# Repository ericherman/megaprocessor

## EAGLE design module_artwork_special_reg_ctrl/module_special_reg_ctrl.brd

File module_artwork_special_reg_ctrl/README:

Special Registers Control

This module generates the control signals for the Special Purpose
Registers module. To do this it uses information from the decoder
modules together with current state (and also the count in H for
iterative instructions) to work out what needs to be done this cycle.

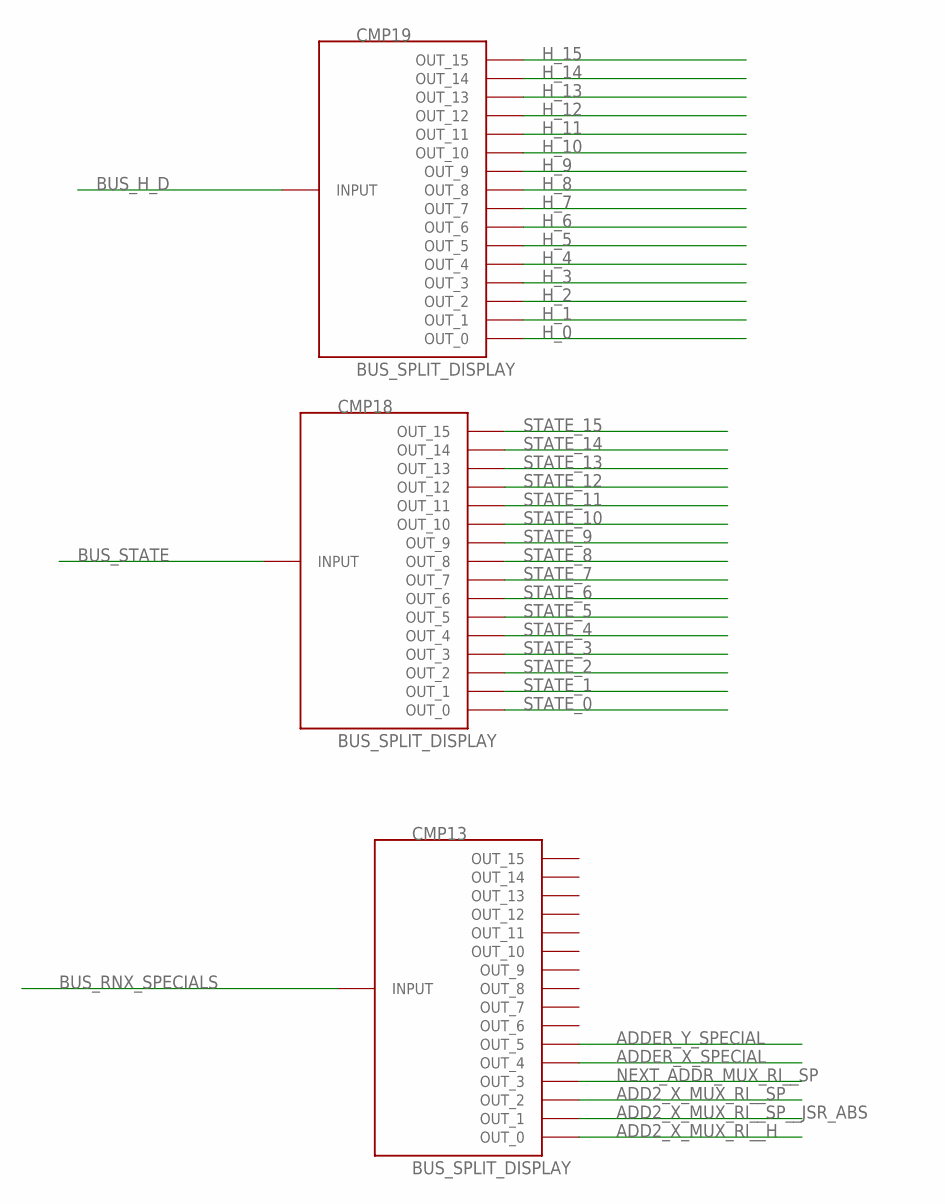
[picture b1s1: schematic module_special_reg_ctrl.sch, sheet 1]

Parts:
CMP13, CMP18, CMP19: BUS_SPLIT_DISPLAY

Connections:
ADD2_X_MUX_RI__H: CMP13.P$1 (OUT_0)
ADD2_X_MUX_RI__SP: CMP13.P$3 (OUT_2)
ADD2_X_MUX_RI__SP__JSR_ABS: CMP13.P$2 (OUT_1); also elsewhere on the board
ADDER_X_SPECIAL: CMP13.P$5 (OUT_4)
ADDER_Y_SPECIAL: CMP13.P$6 (OUT_5)
BUS_H_D: CMP19.INPUT
BUS_RNX_SPECIALS: CMP13.INPUT
BUS_STATE: CMP18.INPUT
H_0: CMP19.P$1 (OUT_0); also elsewhere on the board
H_1: CMP19.P$2 (OUT_1); also elsewhere on the board
H_2: CMP19.P$3 (OUT_2); also elsewhere on the board
H_3: CMP19.P$4 (OUT_3); also elsewhere on the board
H_4: CMP19.P$5 (OUT_4); also elsewhere on the board
H_5: CMP19.P$6 (OUT_5); also elsewhere on the board
H_6: CMP19.P$7 (OUT_6)
H_7: CMP19.P$8 (OUT_7)
H_8: CMP19.P$9 (OUT_8)
H_9: CMP19.P$10 (OUT_9)
H_10: CMP19.P$11 (OUT_10)
H_11: CMP19.P$12 (OUT_11)
H_12: CMP19.P$13 (OUT_12)
H_13: CMP19.P$14 (OUT_13)
H_14: CMP19.P$15 (OUT_14)
H_15: CMP19.P$16 (OUT_15)
NEXT_ADDR_MUX_RI__SP: CMP13.P$4 (OUT_3); also elsewhere on the board
STATE_0: CMP18.P$1 (OUT_0); also elsewhere on the board
STATE_1: CMP18.P$2 (OUT_1); also elsewhere on the board
STATE_2: CMP18.P$3 (OUT_2); also elsewhere on the board
STATE_3: CMP18.P$4 (OUT_3)
STATE_4: CMP18.P$5 (OUT_4); also elsewhere on the board
STATE_5: CMP18.P$6 (OUT_5); also elsewhere on the board
STATE_6: CMP18.P$7 (OUT_6); also elsewhere on the board
STATE_7: CMP18.P$8 (OUT_7); also elsewhere on the board
STATE_8: CMP18.P$9 (OUT_8); also elsewhere on the board
STATE_9: CMP18.P$10 (OUT_9); also elsewhere on the board
STATE_10: CMP18.P$11 (OUT_10); also elsewhere on the board
STATE_11: CMP18.P$12 (OUT_11); also elsewhere on the board
STATE_12: CMP18.P$13 (OUT_12); also elsewhere on the board
STATE_13: CMP18.P$14 (OUT_13); also elsewhere on the board
STATE_14: CMP18.P$15 (OUT_14)
STATE_15: CMP18.P$16 (OUT_15); also elsewhere on the board

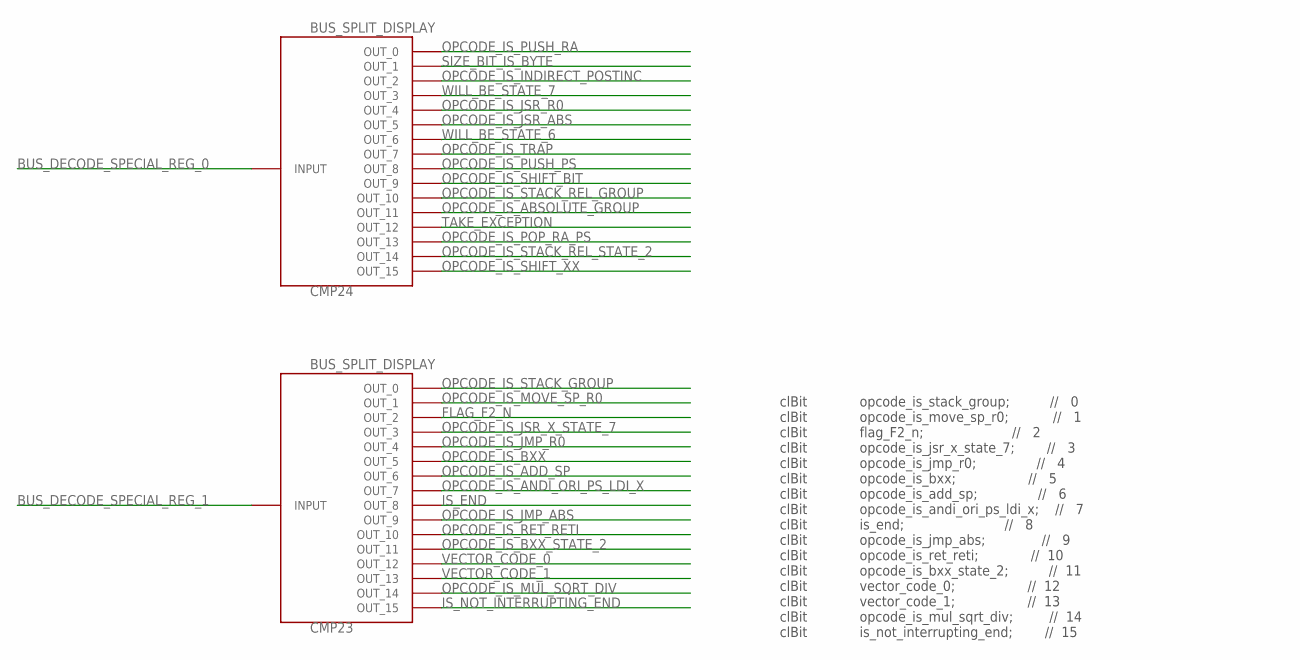
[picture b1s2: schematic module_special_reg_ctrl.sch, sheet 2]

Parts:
CMP23, CMP24: BUS_SPLIT_DISPLAY

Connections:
BUS_DECODE_SPECIAL_REG_0: CMP24.INPUT
BUS_DECODE_SPECIAL_REG_1: CMP23.INPUT
FLAG_F2_N: CMP23.P$3 (OUT_2); also elsewhere on the board
IS_END: CMP23.P$9 (OUT_8); also elsewhere on the board
IS_NOT_INTERRUPTING_END: CMP23.P$16 (OUT_15); also elsewhere on the board
OPCODE_IS_ABSOLUTE_GROUP: CMP24.P$12 (OUT_11); also elsewhere on the board
OPCODE_IS_ADD_SP: CMP23.P$7 (OUT_6); also elsewhere on the board
OPCODE_IS_ANDI_ORI_PS_LDI_X: CMP23.P$8 (OUT_7); also elsewhere on the board
OPCODE_IS_BXX: CMP23.P$6 (OUT_5); also elsewhere on the board
OPCODE_IS_BXX_STATE_2: CMP23.P$12 (OUT_11); also elsewhere on the board
OPCODE_IS_INDIRECT_POSTINC: CMP24.P$3 (OUT_2); also elsewhere on the board
OPCODE_IS_JMP_ABS: CMP23.P$10 (OUT_9); also elsewhere on the board
OPCODE_IS_JMP_R0: CMP23.P$5 (OUT_4); also elsewhere on the board
OPCODE_IS_JSR_ABS: CMP24.P$6 (OUT_5); also elsewhere on the board
OPCODE_IS_JSR_R0: CMP24.P$5 (OUT_4); also elsewhere on the board
OPCODE_IS_JSR_X_STATE_7: CMP23.P$4 (OUT_3); also elsewhere on the board
OPCODE_IS_MOVE_SP_R0: CMP23.P$2 (OUT_1); also elsewhere on the board
OPCODE_IS_MUL_SQRT_DIV: CMP23.P$15 (OUT_14); also elsewhere on the board
OPCODE_IS_POP_RA_PS: CMP24.P$14 (OUT_13); also elsewhere on the board
OPCODE_IS_PUSH_PS: CMP24.P$9 (OUT_8); also elsewhere on the board
OPCODE_IS_PUSH_RA: CMP24.P$1 (OUT_0); also elsewhere on the board
OPCODE_IS_RET_RETI: CMP23.P$11 (OUT_10); also elsewhere on the board
OPCODE_IS_SHIFT_BIT: CMP24.P$10 (OUT_9); also elsewhere on the board
OPCODE_IS_SHIFT_XX: CMP24.P$16 (OUT_15); also elsewhere on the board
OPCODE_IS_STACK_GROUP: CMP23.P$1 (OUT_0); also elsewhere on the board
OPCODE_IS_STACK_REL_GROUP: CMP24.P$11 (OUT_10); also elsewhere on the board
OPCODE_IS_STACK_REL_STATE_2: CMP24.P$15 (OUT_14); also elsewhere on the board
OPCODE_IS_TRAP: CMP24.P$8 (OUT_7); also elsewhere on the board
SIZE_BIT_IS_BYTE: CMP24.P$2 (OUT_1); also elsewhere on the board
TAKE_EXCEPTION: CMP24.P$13 (OUT_12); also elsewhere on the board
VECTOR_CODE_0: CMP23.P$13 (OUT_12); also elsewhere on the board
VECTOR_CODE_1: CMP23.P$14 (OUT_13); also elsewhere on the board
WILL_BE_STATE_6: CMP24.P$7 (OUT_6); also elsewhere on the board
WILL_BE_STATE_7: CMP24.P$4 (OUT_3); also elsewhere on the board

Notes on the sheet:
clBit opcode_is_stack_group; // 0 clBit opcode_is_move_sp_r0; // 1 clBit flag_F2_n; // 2 clBit opcode_is_jsr_x_state_7; // 3 clBit opcode_is_jmp_r0; // 4 clBit opcode_is_bxx; // 5 clBit opcode_is_add_sp; // 6 clBit opcode_is_andi_ori_ps_ldi_x; // 7 clBit is_end; // 8 clBit opcode_is_jmp_abs; // 9 c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

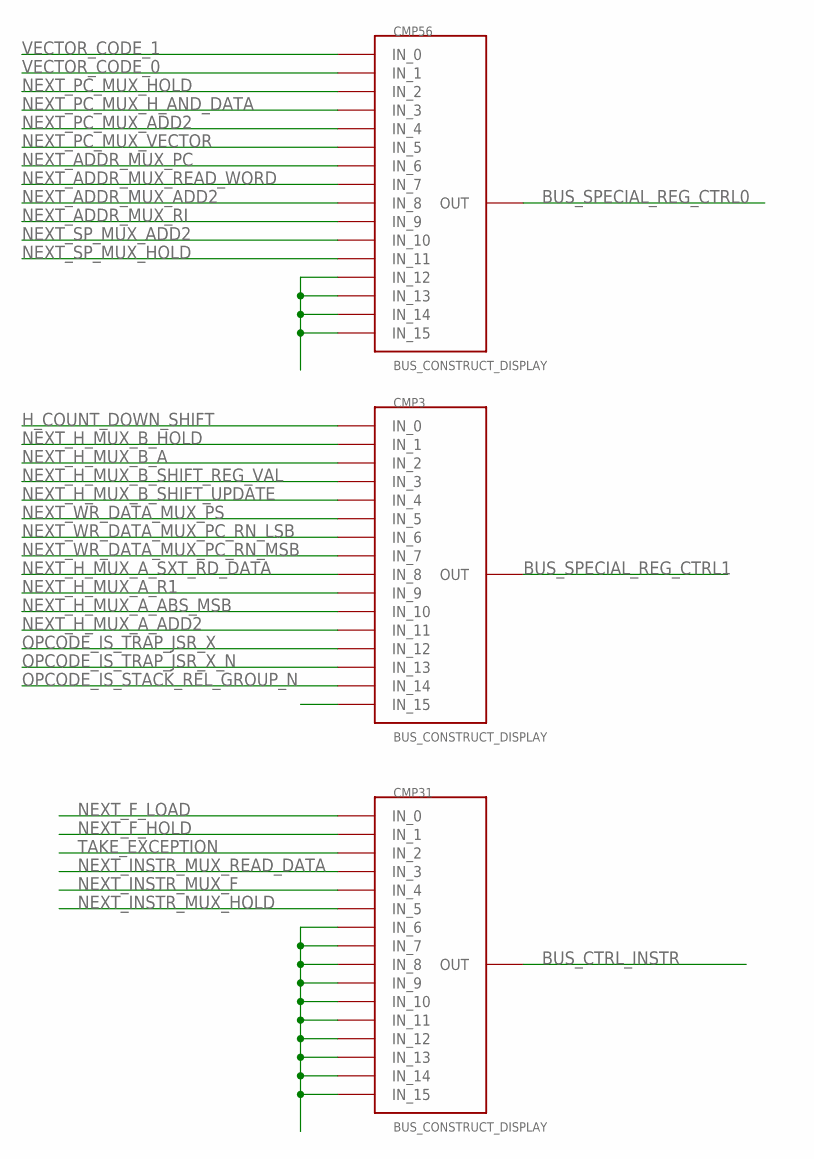
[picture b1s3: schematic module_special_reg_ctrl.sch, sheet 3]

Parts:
CMP3, CMP31, CMP56: BUS_CONSTRUCT_DISPLAY; BUS_SPLIT_DISPLAY

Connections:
BUS_CTRL_INSTR: CMP31.INPUT (OUT)
BUS_SPECIAL_REG_CTRL0: CMP56.INPUT (OUT)
BUS_SPECIAL_REG_CTRL1: CMP3.INPUT (OUT)
H_COUNT_DOWN_SHIFT: CMP3.P$1 (IN_0); also elsewhere on the board
unnamed: CMP56.P$13 (IN_12), CMP56.P$14 (IN_13), CMP56.P$15 (IN_14), CMP56.P$16 (IN_15)
unnamed: CMP31.P$7 (IN_6), CMP31.P$8 (IN_7), CMP31.P$9 (IN_8), CMP31.P$10 (IN_9), CMP31.P$11 (IN_10), CMP31.P$12 (IN_11), CMP31.P$13 (IN_12), CMP31.P$14 (IN_13), CMP31.P$15 (IN_14), CMP31.P$16 (IN_15)
NEXT_ADDR_MUX_ADD2: CMP56.P$9 (IN_8); also elsewhere on the board
NEXT_ADDR_MUX_PC: CMP56.P$7 (IN_6); also elsewhere on the board
NEXT_ADDR_MUX_READ_WORD: CMP56.P$8 (IN_7); also elsewhere on the board
NEXT_ADDR_MUX_RI: CMP56.P$10 (IN_9); also elsewhere on the board
NEXT_F_HOLD: CMP31.P$2 (IN_1); also elsewhere on the board
NEXT_F_LOAD: CMP31.P$1 (IN_0); also elsewhere on the board
NEXT_H_MUX_A_ABS_MSB: CMP3.P$11 (IN_10); also elsewhere on the board
NEXT_H_MUX_A_ADD2: CMP3.P$12 (IN_11); also elsewhere on the board
NEXT_H_MUX_A_R1: CMP3.P$10 (IN_9); also elsewhere on the board
NEXT_H_MUX_A_SXT_RD_DATA: CMP3.P$9 (IN_8); also elsewhere on the board
NEXT_H_MUX_B_A: CMP3.P$3 (IN_2); also elsewhere on the board
NEXT_H_MUX_B_HOLD: CMP3.P$2 (IN_1); also elsewhere on the board
NEXT_H_MUX_B_SHIFT_REG_VAL: CMP3.P$4 (IN_3); also elsewhere on the board
NEXT_H_MUX_B_SHIFT_UPDATE: CMP3.P$5 (IN_4); also elsewhere on the board
NEXT_INSTR_MUX_F: CMP31.P$5 (IN_4); also elsewhere on the board
NEXT_INSTR_MUX_HOLD: CMP31.P$6 (IN_5); also elsewhere on the board
NEXT_INSTR_MUX_READ_DATA: CMP31.P$4 (IN_3); also elsewhere on the board
NEXT_PC_MUX_ADD2: CMP56.P$5 (IN_4); also elsewhere on the board
NEXT_PC_MUX_HOLD: CMP56.P$3 (IN_2); also elsewhere on the board
NEXT_PC_MUX_H_AND_DATA: CMP56.P$4 (IN_3); also elsewhere on the board
NEXT_PC_MUX_VECTOR: CMP56.P$6 (IN_5); also elsewhere on the board
NEXT_SP_MUX_ADD2: CMP56.P$11 (IN_10); also elsewhere on the board
NEXT_SP_MUX_HOLD: CMP56.P$12 (IN_11); also elsewhere on the board
NEXT_WR_DATA_MUX_PC_RN_LSB: CMP3.P$7 (IN_6); also elsewhere on the board
NEXT_WR_DATA_MUX_PC_RN_MSB: CMP3.P$8 (IN_7); also elsewhere on the board
NEXT_WR_DATA_MUX_PS: CMP3.P$6 (IN_5); also elsewhere on the board
OPCODE_IS_STACK_REL_GROUP_N: CMP3.P$15 (IN_14); also elsewhere on the board
OPCODE_IS_TRAP_JSR_X: CMP3.P$13 (IN_12); also elsewhere on the board
OPCODE_IS_TRAP_JSR_X_N: CMP3.P$14 (IN_13); also elsewhere on the board
TAKE_EXCEPTION: CMP31.P$3 (IN_2); also elsewhere on the board
VECTOR_CODE_0: CMP56.P$2 (IN_1); also elsewhere on the board
VECTOR_CODE_1: CMP56.P$1 (IN_0); also elsewhere on the board

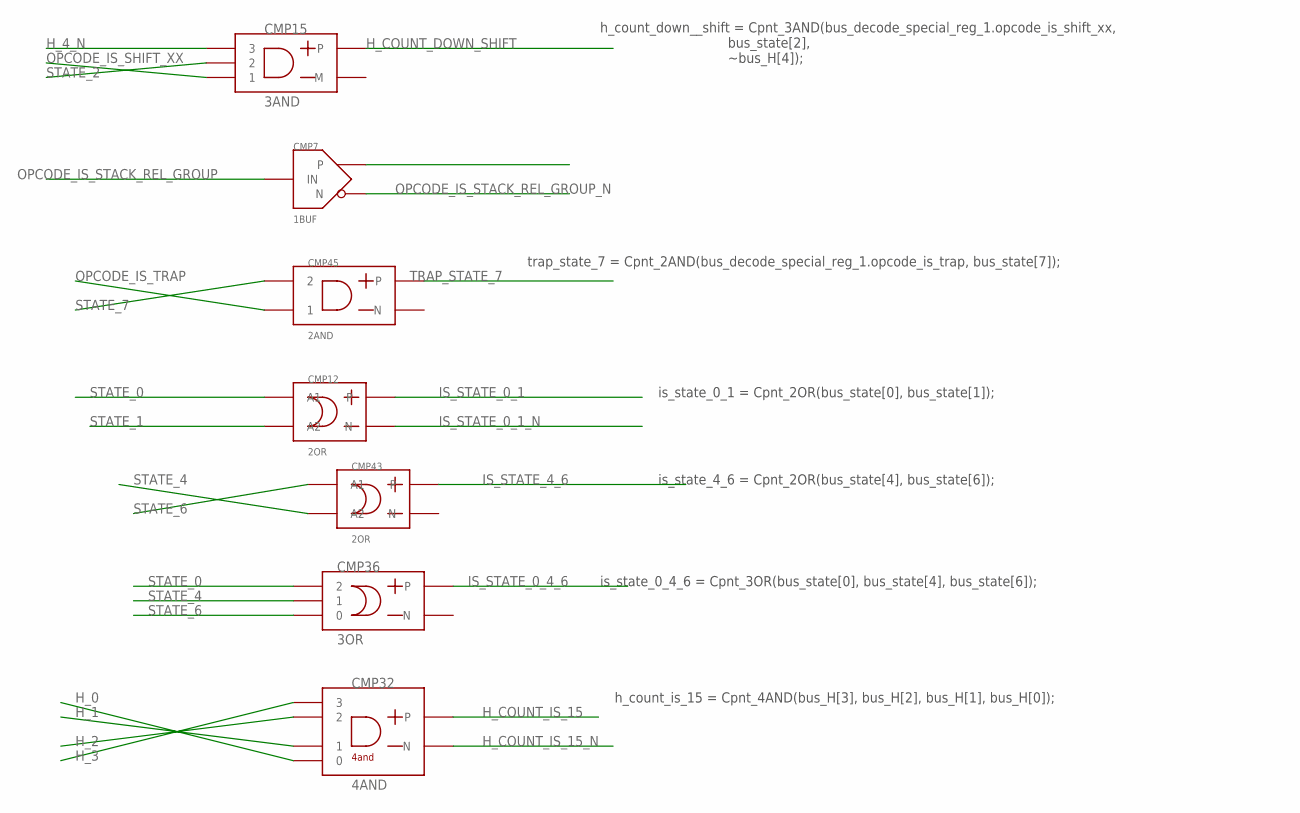
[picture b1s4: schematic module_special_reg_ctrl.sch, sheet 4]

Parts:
CMP7: 1BUF
CMP12, CMP43: 2OR
CMP15: 3AND
CMP32: 4AND
CMP36: 3OR
CMP45: 2AND

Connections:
H_0: CMP32.P$1 (0); also elsewhere on the board
H_1: CMP32.P$2 (1); also elsewhere on the board
H_2: CMP32.P$3 (2); also elsewhere on the board
H_3: CMP32.P$4 (3); also elsewhere on the board
H_4_N: CMP15.P$3 (3); also elsewhere on the board
H_COUNT_DOWN_SHIFT: CMP15.OUT_P; also elsewhere on the board
H_COUNT_IS_15: CMP32.OUT_P; also elsewhere on the board
H_COUNT_IS_15_N: CMP32.OUT_M (N); also elsewhere on the board
IS_STATE_0_1: CMP12.OUT_P; also elsewhere on the board
IS_STATE_0_1_N: CMP12.OUT_M (N); also elsewhere on the board
IS_STATE_0_4_6: CMP36.OUT_P; also elsewhere on the board
IS_STATE_4_6: CMP43.OUT_P; also elsewhere on the board
OPCODE_IS_SHIFT_XX: CMP15.P$1 (1); also elsewhere on the board
OPCODE_IS_STACK_REL_GROUP: CMP7.IN; also elsewhere on the board
OPCODE_IS_STACK_REL_GROUP_N: CMP7.N; also elsewhere on the board
OPCODE_IS_TRAP: CMP45.P$1 (1); also elsewhere on the board
STATE_0: CMP12.P$2 (A1), CMP36.P$3 (2); also elsewhere on the board
STATE_1: CMP12.P$1 (A2); also elsewhere on the board
STATE_2: CMP15.P$2 (2); also elsewhere on the board
STATE_4: CMP36.P$2 (1), CMP43.P$1 (A2); also elsewhere on the board
STATE_6: CMP36.P$1 (0), CMP43.P$2 (A1); also elsewhere on the board
STATE_7: CMP45.P$2 (2); also elsewhere on the board
TRAP_STATE_7: CMP45.OUT_P; also elsewhere on the board

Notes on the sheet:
h_count_down__shift = Cpnt_3AND(bus_decode_special_reg_1.opcode_is_shift_xx, bus_state[2], ~bus_H[4]);
trap_state_7 = Cpnt_2AND(bus_decode_special_reg_1.opcode_is_trap, bus_state[7]);
is_state_0_1 = Cpnt_2OR(bus_state[0], bus_state[1]);
is_state_4_6 = Cpnt_2OR(bus_state[4], bus_state[6]);
is_state_0_4_6 = Cpnt_3OR(bus_state[0], bus_state[4], bus_state[6]);
h_count_is_15 = Cpnt_4AND(bus_H[3], bus_H[2], bus_H[1], bus_H[0]);

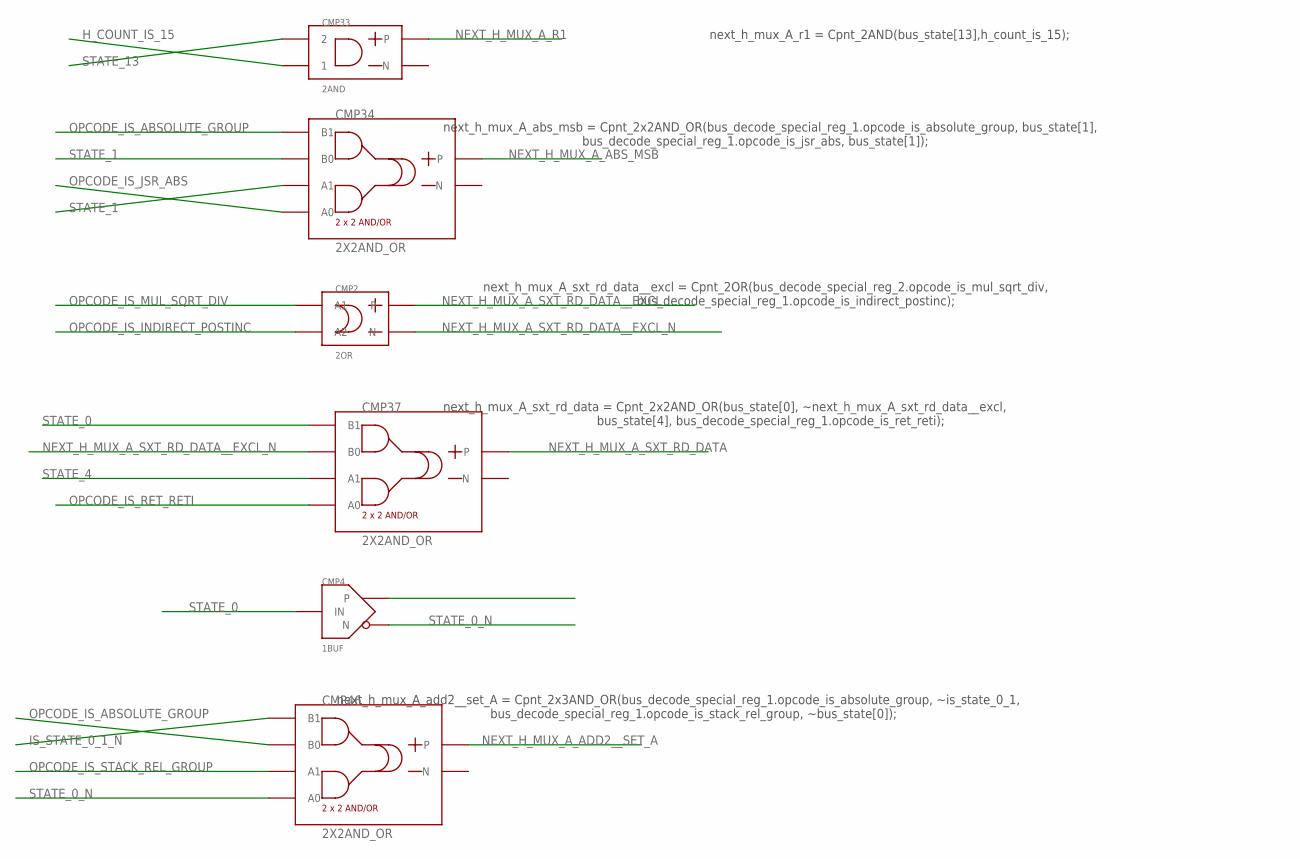
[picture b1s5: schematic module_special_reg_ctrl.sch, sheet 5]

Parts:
CMP2: 2OR
CMP4: 1BUF
CMP33: 2AND
CMP34, CMP37, CMP46: 2X2AND_OR

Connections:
H_COUNT_IS_15: CMP33.P$1 (1); also elsewhere on the board
IS_STATE_0_1_N: CMP46.P$4 (B1); also elsewhere on the board
NEXT_H_MUX_A_ABS_MSB: CMP34.OUT_P; also elsewhere on the board
NEXT_H_MUX_A_ADD2__SET_A: CMP46.OUT_P; also elsewhere on the board
NEXT_H_MUX_A_R1: CMP33.OUT_P; also elsewhere on the board
NEXT_H_MUX_A_SXT_RD_DATA: CMP37.OUT_P; also elsewhere on the board
NEXT_H_MUX_A_SXT_RD_DATA__EXCL: CMP2.OUT_P
NEXT_H_MUX_A_SXT_RD_DATA__EXCL_N: CMP2.OUT_M (N), CMP37.P$3 (B0)
OPCODE_IS_ABSOLUTE_GROUP: CMP34.P$4 (B1), CMP46.P$3 (B0); also elsewhere on the board
OPCODE_IS_INDIRECT_POSTINC: CMP2.P$1 (A2); also elsewhere on the board
OPCODE_IS_JSR_ABS: CMP34.P$1 (A0); also elsewhere on the board
OPCODE_IS_MUL_SQRT_DIV: CMP2.P$2 (A1); also elsewhere on the board
OPCODE_IS_RET_RETI: CMP37.P$1 (A0); also elsewhere on the board
OPCODE_IS_STACK_REL_GROUP: CMP46.P$2 (A1); also elsewhere on the board
STATE_0: CMP4.IN, CMP37.P$4 (B1); also elsewhere on the board
STATE_0_N: CMP4.N, CMP46.P$1 (A0)
STATE_1: CMP34.P$2 (A1), CMP34.P$3 (B0); also elsewhere on the board
STATE_4: CMP37.P$2 (A1); also elsewhere on the board
STATE_13: CMP33.P$2 (2); also elsewhere on the board

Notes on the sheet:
next_h_mux_A_r1 = Cpnt_2AND(bus_state[13],h_count_is_15);
next_h_mux_A_abs_msb = Cpnt_2x2AND_OR(bus_decode_special_reg_1.opcode_is_absolute_group, bus_state[1], bus_decode_special_reg_1.opcode_is_jsr_abs, bus_state[1]);
next_h_mux_A_sxt_rd_data__excl = Cpnt_2OR(bus_decode_special_reg_2.opcode_is_mul_sqrt_div, bus_decode_special_reg_1.opcode_is_indirect_postinc);
next_h_mux_A_sxt_rd_data = Cpnt_2x2AND_OR(bus_state[0], ~next_h_mux_A_sxt_rd_data__excl, bus_state[4], bus_decode_special_reg_1.opcode_is_ret_reti);
next_h_mux_A_add2__set_A = Cpnt_2x3AND_OR(bus_decode_special_reg_1.opcode_is_absolute_group, ~is_state_0_1, bus_decode_special_reg_1.opcode_is_stack_rel_group, ~bus_state[0]);

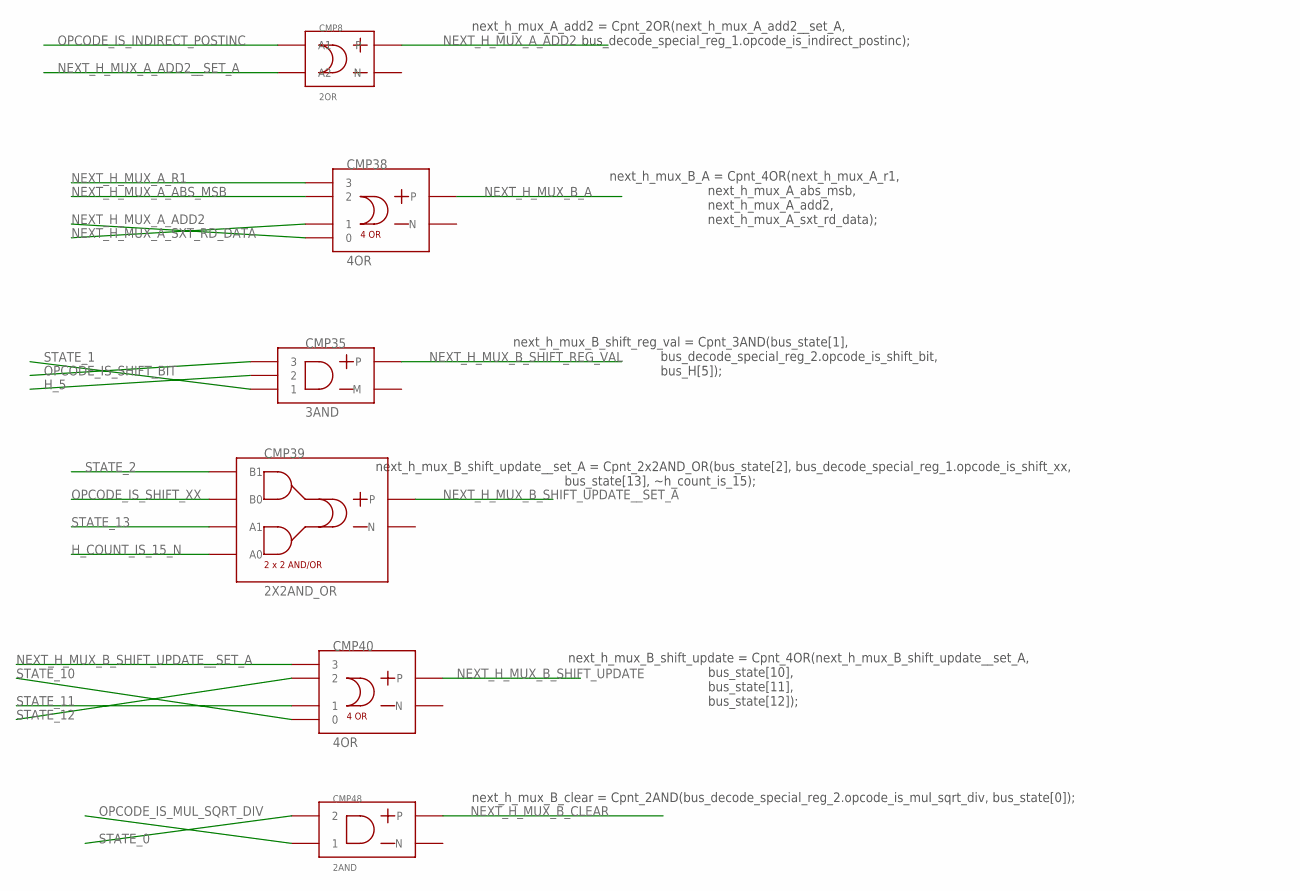
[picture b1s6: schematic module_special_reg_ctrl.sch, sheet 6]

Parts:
CMP8: 2OR
CMP35: 3AND
CMP38, CMP40: 4OR
CMP39: 2X2AND_OR
CMP48: 2AND

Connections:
H_5: CMP35.P$2 (2); also elsewhere on the board
H_COUNT_IS_15_N: CMP39.P$1 (A0); also elsewhere on the board
NEXT_H_MUX_A_ABS_MSB: CMP38.3 (2); also elsewhere on the board
NEXT_H_MUX_A_ADD2: CMP8.OUT_P, CMP38.1 (0); also elsewhere on the board
NEXT_H_MUX_A_ADD2__SET_A: CMP8.P$1 (A2); also elsewhere on the board
NEXT_H_MUX_A_R1: CMP38.4 (3); also elsewhere on the board
NEXT_H_MUX_A_SXT_RD_DATA: CMP38.2 (1); also elsewhere on the board
NEXT_H_MUX_B_A: CMP38.OUT_P; also elsewhere on the board
NEXT_H_MUX_B_CLEAR: CMP48.OUT_P; also elsewhere on the board
NEXT_H_MUX_B_SHIFT_REG_VAL: CMP35.OUT_P; also elsewhere on the board
NEXT_H_MUX_B_SHIFT_UPDATE: CMP40.OUT_P; also elsewhere on the board
NEXT_H_MUX_B_SHIFT_UPDATE__SET_A: CMP39.OUT_P, CMP40.4 (3)
OPCODE_IS_INDIRECT_POSTINC: CMP8.P$2 (A1); also elsewhere on the board
OPCODE_IS_MUL_SQRT_DIV: CMP48.P$1 (1); also elsewhere on the board
OPCODE_IS_SHIFT_BIT: CMP35.P$3 (3); also elsewhere on the board
OPCODE_IS_SHIFT_XX: CMP39.P$3 (B0); also elsewhere on the board
STATE_0: CMP48.P$2 (2); also elsewhere on the board
STATE_1: CMP35.P$1 (1); also elsewhere on the board
STATE_2: CMP39.P$4 (B1); also elsewhere on the board
STATE_10: CMP40.1 (0); also elsewhere on the board
STATE_11: CMP40.2 (1); also elsewhere on the board
STATE_12: CMP40.3 (2); also elsewhere on the board
STATE_13: CMP39.P$2 (A1); also elsewhere on the board

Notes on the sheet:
next_h_mux_A_add2 = Cpnt_2OR(next_h_mux_A_add2__set_A, bus_decode_special_reg_1.opcode_is_indirect_postinc);
next_h_mux_B_A = Cpnt_4OR(next_h_mux_A_r1, next_h_mux_A_abs_msb, next_h_mux_A_add2, next_h_mux_A_sxt_rd_data);
next_h_mux_B_shift_reg_val = Cpnt_3AND(bus_state[1], bus_decode_special_reg_2.opcode_is_shift_bit, bus_H[5]);
next_h_mux_B_shift_update__set_A = Cpnt_2x2AND_OR(bus_state[2], bus_decode_special_reg_1.opcode_is_shift_xx, bus_state[13], ~h_count_is_15);
next_h_mux_B_shift_update = Cpnt_4OR(next_h_mux_B_shift_update__set_A, bus_state[10], bus_state[11], bus_state[12]);
next_h_mux_B_clear = Cpnt_2AND(bus_decode_special_reg_2.opcode_is_mul_sqrt_div, bus_state[0]);

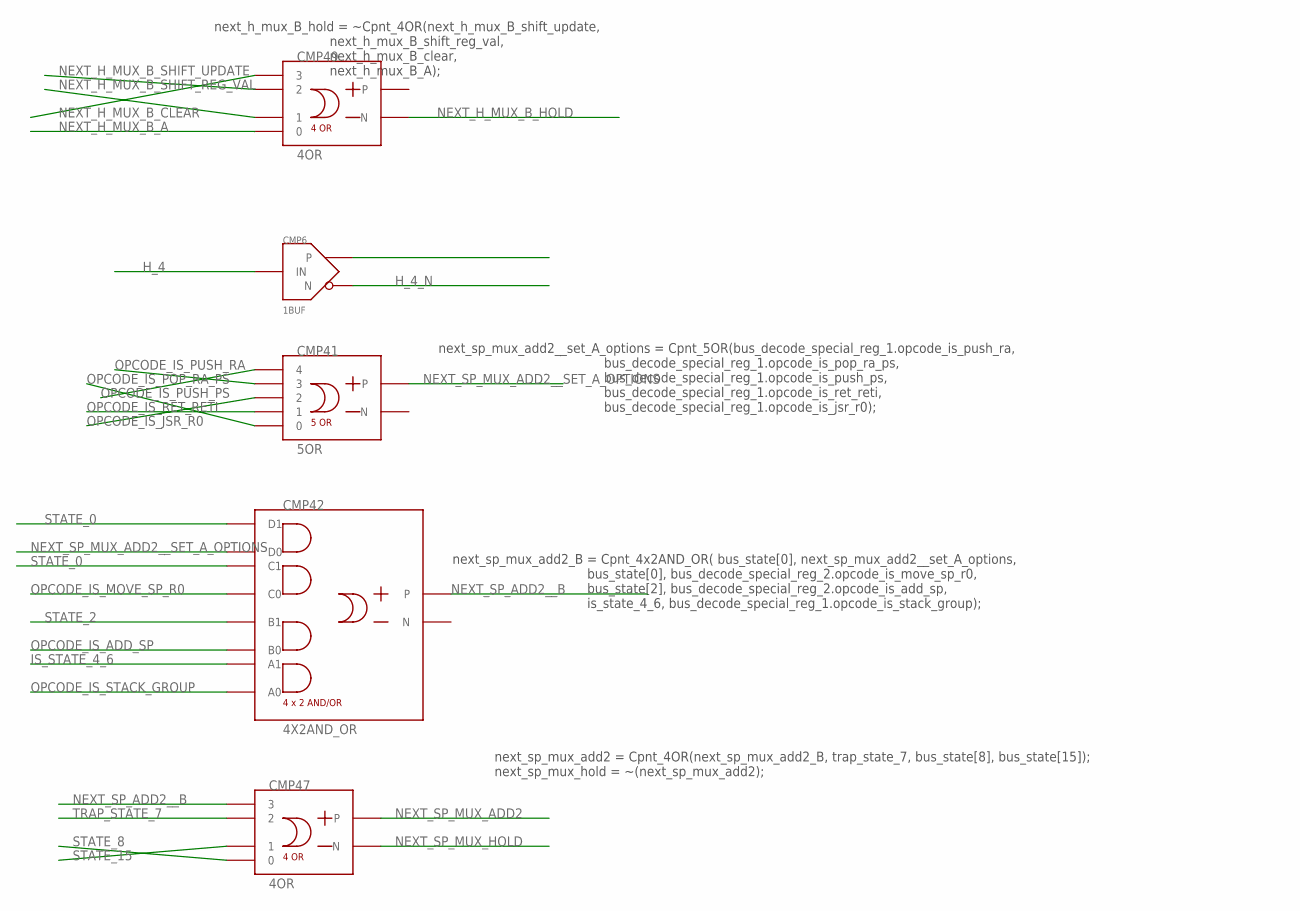
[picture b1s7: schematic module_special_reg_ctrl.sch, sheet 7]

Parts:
CMP6: 1BUF
CMP41: 5OR
CMP42: 4X2AND_OR
CMP47, CMP49: 4OR

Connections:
H_4: CMP6.IN; also elsewhere on the board
H_4_N: CMP6.N; also elsewhere on the board
IS_STATE_4_6: CMP42.P$2 (A1); also elsewhere on the board
NEXT_H_MUX_B_A: CMP49.1 (0); also elsewhere on the board
NEXT_H_MUX_B_CLEAR: CMP49.4 (3); also elsewhere on the board
NEXT_H_MUX_B_HOLD: CMP49.OUT_M (N); also elsewhere on the board
NEXT_H_MUX_B_SHIFT_REG_VAL: CMP49.2 (1); also elsewhere on the board
NEXT_H_MUX_B_SHIFT_UPDATE: CMP49.3 (2); also elsewhere on the board
NEXT_SP_ADD2__B: CMP42.OUT_P, CMP47.4 (3)
NEXT_SP_MUX_ADD2: CMP47.OUT_P; also elsewhere on the board
NEXT_SP_MUX_ADD2__SET_A_OPTIONS: CMP41.OUT_P, CMP42.P$7 (D0)
NEXT_SP_MUX_HOLD: CMP47.OUT_M (N); also elsewhere on the board
OPCODE_IS_ADD_SP: CMP42.P$3 (B0); also elsewhere on the board
OPCODE_IS_JSR_R0: CMP41.3 (2); also elsewhere on the board
OPCODE_IS_MOVE_SP_R0: CMP42.P$5 (C0); also elsewhere on the board
OPCODE_IS_POP_RA_PS: CMP41.1 (0); also elsewhere on the board
OPCODE_IS_PUSH_PS: CMP41.5 (4); also elsewhere on the board
OPCODE_IS_PUSH_RA: CMP41.4 (3); also elsewhere on the board
OPCODE_IS_RET_RETI: CMP41.2 (1); also elsewhere on the board
OPCODE_IS_STACK_GROUP: CMP42.P$1 (A0); also elsewhere on the board
STATE_0: CMP42.P$6 (C1), CMP42.P$8 (D1); also elsewhere on the board
STATE_2: CMP42.P$4 (B1); also elsewhere on the board
STATE_8: CMP47.1 (0); also elsewhere on the board
STATE_15: CMP47.2 (1); also elsewhere on the board
TRAP_STATE_7: CMP47.3 (2); also elsewhere on the board

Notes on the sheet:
next_h_mux_B_hold = ~Cpnt_4OR(next_h_mux_B_shift_update, next_h_mux_B_shift_reg_val, next_h_mux_B_clear, next_h_mux_B_A);
next_sp_mux_add2__set_A_options = Cpnt_5OR(bus_decode_special_reg_1.opcode_is_push_ra, bus_decode_special_reg_1.opcode_is_pop_ra_ps, bus_decode_special_reg_1.opcode_is_push_ps, bus_decode_special_reg_1.opcode_is_ret_reti, bus_decode_special_reg_1.opcode_is_jsr_r0);
next_sp_mux_add2_B = Cpnt_4x2AND_OR( bus_state[0], next_sp_mux_add2__set_A_options, bus_state[0], bus_decode_special_reg_2.opcode_is_move_sp_r0, bus_state[2], bus_decode_special_reg_2.opcode_is_add_sp, is_state_4_6, bus_decode_special_reg_1.opcode_is_stack_group);
next_sp_mux_add2 = Cpnt_4OR(next_sp_mux_add2_B, trap_state_7, bus_state[8], bus_state[15]); next_sp_mux_hold = ~(next_sp_mux_add2);

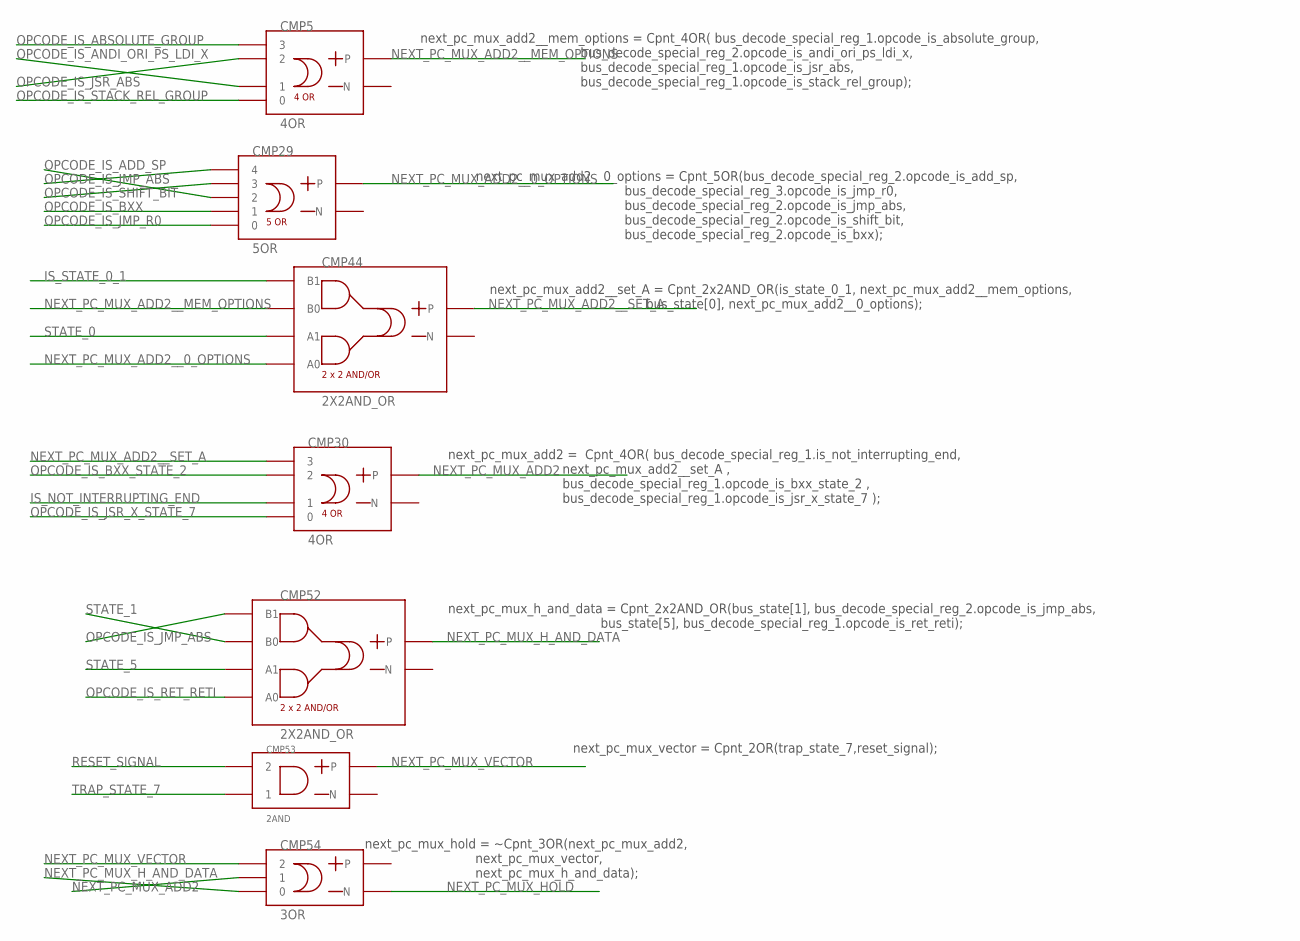
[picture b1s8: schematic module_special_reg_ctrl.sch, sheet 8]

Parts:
CMP5, CMP30: 4OR
CMP29: 5OR
CMP44, CMP52: 2X2AND_OR
CMP53: 2AND
CMP54: 3OR

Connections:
IS_NOT_INTERRUPTING_END: CMP30.2 (1); also elsewhere on the board
IS_STATE_0_1: CMP44.P$4 (B1); also elsewhere on the board
NEXT_PC_MUX_ADD2: CMP30.OUT_P, CMP54.P$2 (1); also elsewhere on the board
NEXT_PC_MUX_ADD2__0_OPTIONS: CMP29.OUT_P, CMP44.P$1 (A0)
NEXT_PC_MUX_ADD2__MEM_OPTIONS: CMP5.OUT_P, CMP44.P$3 (B0)
NEXT_PC_MUX_ADD2__SET_A: CMP30.4 (3), CMP44.OUT_P
NEXT_PC_MUX_HOLD: CMP54.OUT_M (N); also elsewhere on the board
NEXT_PC_MUX_H_AND_DATA: CMP52.OUT_P, CMP54.P$1 (0); also elsewhere on the board
NEXT_PC_MUX_VECTOR: CMP53.OUT_P, CMP54.P$3 (2); also elsewhere on the board
OPCODE_IS_ABSOLUTE_GROUP: CMP5.4 (3); also elsewhere on the board
OPCODE_IS_ADD_SP: CMP29.3 (2); also elsewhere on the board
OPCODE_IS_ANDI_ORI_PS_LDI_X: CMP5.2 (1); also elsewhere on the board
OPCODE_IS_BXX: CMP29.2 (1); also elsewhere on the board
OPCODE_IS_BXX_STATE_2: CMP30.3 (2); also elsewhere on the board
OPCODE_IS_JMP_ABS: CMP29.5 (4), CMP52.P$4 (B1); also elsewhere on the board
OPCODE_IS_JMP_R0: CMP29.1 (0); also elsewhere on the board
OPCODE_IS_JSR_ABS: CMP5.3 (2); also elsewhere on the board
OPCODE_IS_JSR_X_STATE_7: CMP30.1 (0); also elsewhere on the board
OPCODE_IS_RET_RETI: CMP52.P$1 (A0); also elsewhere on the board
OPCODE_IS_SHIFT_BIT: CMP29.4 (3); also elsewhere on the board
OPCODE_IS_STACK_REL_GROUP: CMP5.1 (0); also elsewhere on the board
RESET_SIGNAL: CMP53.P$2 (2)
STATE_0: CMP44.P$2 (A1); also elsewhere on the board
STATE_1: CMP52.P$3 (B0); also elsewhere on the board
STATE_5: CMP52.P$2 (A1); also elsewhere on the board
TRAP_STATE_7: CMP53.P$1 (1); also elsewhere on the board

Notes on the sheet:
next_pc_mux_add2__mem_options = Cpnt_4OR( bus_decode_special_reg_1.opcode_is_absolute_group, bus_decode_special_reg_2.opcode_is_andi_ori_ps_ldi_x, bus_decode_special_reg_1.opcode_is_jsr_abs, bus_decode_special_reg_1.opcode_is_stack_rel_group);
next_pc_mux_add2__0_options = Cpnt_5OR(bus_decode_special_reg_2.opcode_is_add_sp, bus_decode_special_reg_3.opcode_is_jmp_r0, bus_decode_special_reg_2.opcode_is_jmp_abs, bus_decode_special_reg_2.opcode_is_shift_bit, bus_decode_special_reg_2.opcode_is_bxx);
next_pc_mux_add2__set_A = Cpnt_2x2AND_OR(is_state_0_1, next_pc_mux_add2__mem_options, bus_state[0], next_pc_mux_add2__0_options);
next_pc_mux_add2 = Cpnt_4OR( bus_decode_special_reg_1.is_not_interrupting_end, next_pc_mux_add2__set_A , bus_decode_special_reg_1.opcode_is_bxx_state_2 , bus_decode_special_reg_1.opcode_is_jsr_x_state_7 );
next_pc_mux_h_and_data = Cpnt_2x2AND_OR(bus_state[1], bus_decode_special_reg_2.opcode_is_jmp_abs, bus_state[5], bus_decode_special_reg_1.opcode_is_ret_reti);
next_pc_mux_vector = Cpnt_2OR(trap_state_7,reset_signal);
next_pc_mux_hold = ~Cpnt_3OR(next_pc_mux_add2, next_pc_mux_vector, next_pc_mux_h_and_data);

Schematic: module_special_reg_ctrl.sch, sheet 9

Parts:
CMP9: 4OR
CMP10: 4X2AND_OR
CMP11: 5OR
CMP16, CMP67: 2AND
CMP22: 1BUF

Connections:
ADD2_X_MUX_RI__SP__JSR_ABS: CMP11.2 (1); also elsewhere on the board
FLAG_F2_N: CMP67.P$1 (1); also elsewhere on the board
IS_END: CMP22.IN; also elsewhere on the board
IS_END_N: CMP10.P$7 (D0), CMP22.N
IS_STATE_4_6: CMP10.P$5 (C0); also elsewhere on the board
NEXT_ADDR_MUX_ADD2: CMP11.OUT_P; also elsewhere on the board
NEXT_ADDR_MUX_ADD2__SET_A: CMP10.OUT_P, CMP11.5 (4)
NEXT_ADDR_MUX_ADD2__SET_A_OPTIONS: CMP9.OUT_P, CMP10.P$2 (A1), CMP10.P$3 (B0)
NEXT_ADDR_MUX_READ_WORD: CMP16.OUT_P; also elsewhere on the board
NON_RESET_TRAP: CMP9.4 (3), CMP67.OUT_P
OPCODE_IS_ABSOLUTE_GROUP: CMP10.P$6 (C1), CMP16.P$1 (1); also elsewhere on the board
OPCODE_IS_BXX_STATE_2: CMP11.4 (3); also elsewhere on the board
OPCODE_IS_JSR_R0: CMP9.1 (0); also elsewhere on the board
OPCODE_IS_PUSH_PS: CMP9.3 (2); also elsewhere on the board
OPCODE_IS_PUSH_RA: CMP9.2 (1); also elsewhere on the board
OPCODE_IS_STACK_REL_GROUP: CMP10.P$8 (D1); also elsewhere on the board
OPCODE_IS_TRAP: CMP67.P$2 (2); also elsewhere on the board
STATE_0: CMP10.P$4 (B1); also elsewhere on the board
STATE_1: CMP16.P$2 (2); also elsewhere on the board
STATE_6: CMP10.P$1 (A0); also elsewhere on the board
STATE_15: CMP11.1 (0); also elsewhere on the board
TRAP_STATE_7: CMP11.3 (2); also elsewhere on the board

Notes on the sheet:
non_reset_trap = Cpnt_2AND(bus_decode_special_reg_2.flag_F2_n, bus_decode_special_reg_1.opcode_is_trap);
next_addr_mux_add2__set_A_options = Cpnt_4OR(bus_decode_special_reg_1.opcode_is_jsr_r0, bus_decode_special_reg_1.opcode_is_push_ra, bus_decode_special_reg_1.opcode_is_push_ps, non_reset_trap);
next_addr_mux_add2__set_A = Cpnt_4x2AND_OR(next_addr_mux_add2__set_A_options,bus_state[0], next_addr_mux_add2__set_A_options,bus_state[6], bus_decode_special_reg_1.opcode_is_stack_rel_group, ~bus_decode_special_reg_2.is_end, bus_decode_special_reg_1.opcode_is_absolute_group, is_state_4_6);
next_addr_mux_add2 = Cpnt_5OR(next_addr_mux_add2__set_A, bus_decode_special_reg_2.opcode_is_bxx_state_2, bus_rnx_specials.add2_x_mux_ri__sp__jsr_abs, bus_state[15], trap_state_7);
next_addr_mux_read_word = Cpnt_2AND(bus_state[1], bus_decode_special_reg_1.opcode_is_absolute_group);

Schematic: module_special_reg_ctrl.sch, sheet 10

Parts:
CMP1, CMP61: 3OR
CMP20: 2X2AND_OR
CMP57: 2OR
CMP58: 5OR
CMP59, CMP60: 3AND
CMP62: 1BUF

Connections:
IS_END: CMP59.P$1 (1), CMP60.P$3 (3); also elsewhere on the board
IS_STATE_0_4_6: CMP20.P$4 (B1); also elsewhere on the board
NEXT_ADDR_MUX_ADD2: CMP1.P$2 (1); also elsewhere on the board
NEXT_ADDR_MUX_PC: CMP1.OUT_M (N); also elsewhere on the board
NEXT_ADDR_MUX_READ_WORD: CMP1.P$1 (0); also elsewhere on the board
NEXT_ADDR_MUX_RI: CMP1.P$3 (2), CMP20.OUT_P; also elsewhere on the board
NEXT_ADDR_MUX_RI__SP: CMP20.P$1 (A0), CMP20.P$2 (A1); also elsewhere on the board
NEXT_F_HOLD: CMP57.OUT_M (N); also elsewhere on the board
NEXT_F_LOAD: CMP57.OUT_P; also elsewhere on the board
NEXT_INSTR_MUX_F: CMP59.OUT_P, CMP61.P$3 (2); also elsewhere on the board
NEXT_INSTR_MUX_F_N: CMP59.OUT_M (M), CMP60.P$2 (2)
NEXT_INSTR_MUX_F__OPTIONS: CMP58.OUT_P, CMP59.P$2 (2)
NEXT_INSTR_MUX_HOLD: CMP61.OUT_M (N); also elsewhere on the board
NEXT_INSTR_MUX_READ_DATA: CMP60.OUT_P, CMP61.P$2 (1); also elsewhere on the board
OPCODE_IS_INDIRECT_POSTINC: CMP20.P$3 (B0), CMP58.2 (1); also elsewhere on the board
OPCODE_IS_POP_RA_PS: CMP58.5 (4); also elsewhere on the board
OPCODE_IS_PUSH_PS: CMP58.4 (3); also elsewhere on the board
OPCODE_IS_PUSH_RA: CMP58.1 (0); also elsewhere on the board
OPCODE_IS_STACK_REL_GROUP: CMP58.3 (2); also elsewhere on the board
OPCODE_IS_STACK_REL_STATE_2: CMP57.P$2 (A1); also elsewhere on the board
STATE_0: CMP57.P$1 (A2); also elsewhere on the board
TAKE_EXCEPTION: CMP61.P$1 (0), CMP62.IN; also elsewhere on the board
TAKE_EXCEPTION_N: CMP59.P$3 (3), CMP60.P$1 (1), CMP62.N

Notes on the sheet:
next_addr_mux_ri = Cpnt_2x2AND_OR(is_state_0_4_6, bus_decode_special_reg_1.opcode_is_indirect_postinc, bus_rnx_specials.next_addr_mux_ri__sp, bus_rnx_specials.next_addr_mux_ri__sp);
next_addr_mux_pc = ~Cpnt_3OR( next_addr_mux_ri , next_addr_mux_add2 , next_addr_mux_read_word);
next_f_load = Cpnt_2OR(bus_state[0], bus_decode_special_reg_2.opcode_is_stack_rel_state_2); next_f_hold = ~next_f_load;
next_instr_mux_f__options = Cpnt_5OR( bus_decode_special_reg_1.opcode_is_push_ra, bus_decode_special_reg_1.opcode_is_pop_ra_ps, bus_decode_special_reg_1.opcode_is_push_ps, bus_decode_special_reg_1.opcode_is_indirect_postinc, bus_decode_special_reg_1.opcode_is_stack_rel_group);
next_instr_mux_f = Cpnt_3AND(bus_decode_special_reg_2.is_end, ~bus_decode_special_reg_2.take_exception, next_instr_mux_f__options);
next_instr_mux_read_data = Cpnt_3AND(bus_decode_special_reg_2.is_end, ~next_instr_mux_f, ~bus_decode_special_reg_2.take_exception);
next_instr_mux_hold = ~Cpnt_3OR(next_instr_mux_read_data, next_instr_mux_f, bus_decode_special_reg_2.take_exception);

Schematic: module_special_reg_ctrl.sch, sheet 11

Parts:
CMP14: 3OR
CMP17: 2X2AND_OR
CMP21: 3AND
CMP25: 4OR
CMP26: 4X2AND_OR

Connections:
NEXT_WR_DATA_MUX_PC_RA_LSB__7: CMP21.OUT_P, CMP26.P$1 (A0)
NEXT_WR_DATA_MUX_PC_RN_LSB: CMP26.OUT_P; also elsewhere on the board
NEXT_WR_DATA_MUX_PS: CMP17.OUT_P; also elsewhere on the board
NEXT_WR_DATA_MUX_PS_N: CMP17.OUT_M (N), CMP21.P$3 (3)
OPCODE_IS_JSR_ABS: CMP14.P$2 (1), CMP25.1 (0); also elsewhere on the board
OPCODE_IS_JSR_R0: CMP14.P$1 (0), CMP25.2 (1); also elsewhere on the board
OPCODE_IS_PUSH_PS: CMP17.P$4 (B1); also elsewhere on the board
OPCODE_IS_PUSH_RA: CMP25.3 (2), CMP26.P$3 (B0); also elsewhere on the board
OPCODE_IS_TRAP: CMP14.P$3 (2), CMP25.4 (3); also elsewhere on the board
OPCODE_IS_TRAP_JSR_X: CMP14.OUT_P, CMP26.P$8 (D1); also elsewhere on the board
OPCODE_IS_TRAP_JSR_X_N: CMP14.OUT_M (N), CMP21.P$2 (2); also elsewhere on the board
OPCODE_IS_TRAP_JSR_X_PUSH_RA: CMP25.OUT_P
OPCODE_IS_TRAP_JSR_X_PUSH_RA_N: CMP25.OUT_M (N), CMP26.P$5 (C0)
SIZE_BIT_IS_BYTE: CMP21.P$1 (1); also elsewhere on the board
STATE_0: CMP17.P$3 (B0); also elsewhere on the board
STATE_6: CMP26.P$4 (B1), CMP26.P$7 (D0); also elsewhere on the board
TRAP_STATE_7: CMP17.P$1 (A0), CMP17.P$2 (A1); also elsewhere on the board
WILL_BE_STATE_6: CMP26.P$6 (C1); also elsewhere on the board
WILL_BE_STATE_7: CMP26.P$2 (A1); also elsewhere on the board

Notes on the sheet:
opcode_is_trap_jsr_x = Cpnt_3OR(bus_decode_special_reg_1.opcode_is_trap , bus_decode_special_reg_1.opcode_is_jsr_r0, bus_decode_special_reg_1.opcode_is_jsr_abs); next_wr_data_wide_mux_pc = opcode_is_trap_jsr_x; next_wr_data_wide_mux_ra = ~opcode_is_trap_jsr_x;
next_wr_data_mux_ps = Cpnt_2x2AND_OR( bus_state[0], bus_decode_special_reg_1.opcode_is_push_ps, trap_state_7, trap_state_7);
next_wr_data_mux_pc_rn_lsb__7 = Cpnt_3AND(~next_wr_data_mux_ps, ~opcode_is_trap_jsr_x, bus_decode_special_reg_2.size_bit_is_byte);
opcode_is_trap_jsr_x_push_ra = Cpnt_4OR(bus_decode_special_reg_1.opcode_is_trap , bus_decode_special_reg_1.opcode_is_jsr_r0, bus_decode_special_reg_1.opcode_is_jsr_abs, bus_decode_special_reg_1.opcode_is_push_ra);
next_wr_data_mux_pc_rn_lsb = Cpnt_4x2AND_OR(opcode_is_trap_jsr_x, bus_state[6], bus_decode_special_reg_2.will_be_6, ~opcode_is_trap_jsr_x_push_ra, bus_state[6], bus_decode_special_reg_1.opcode_is_push_ra, bus_decode_special_reg_2.will_be_7, next_wr_data_mux_pc_rn_lsb__7);
